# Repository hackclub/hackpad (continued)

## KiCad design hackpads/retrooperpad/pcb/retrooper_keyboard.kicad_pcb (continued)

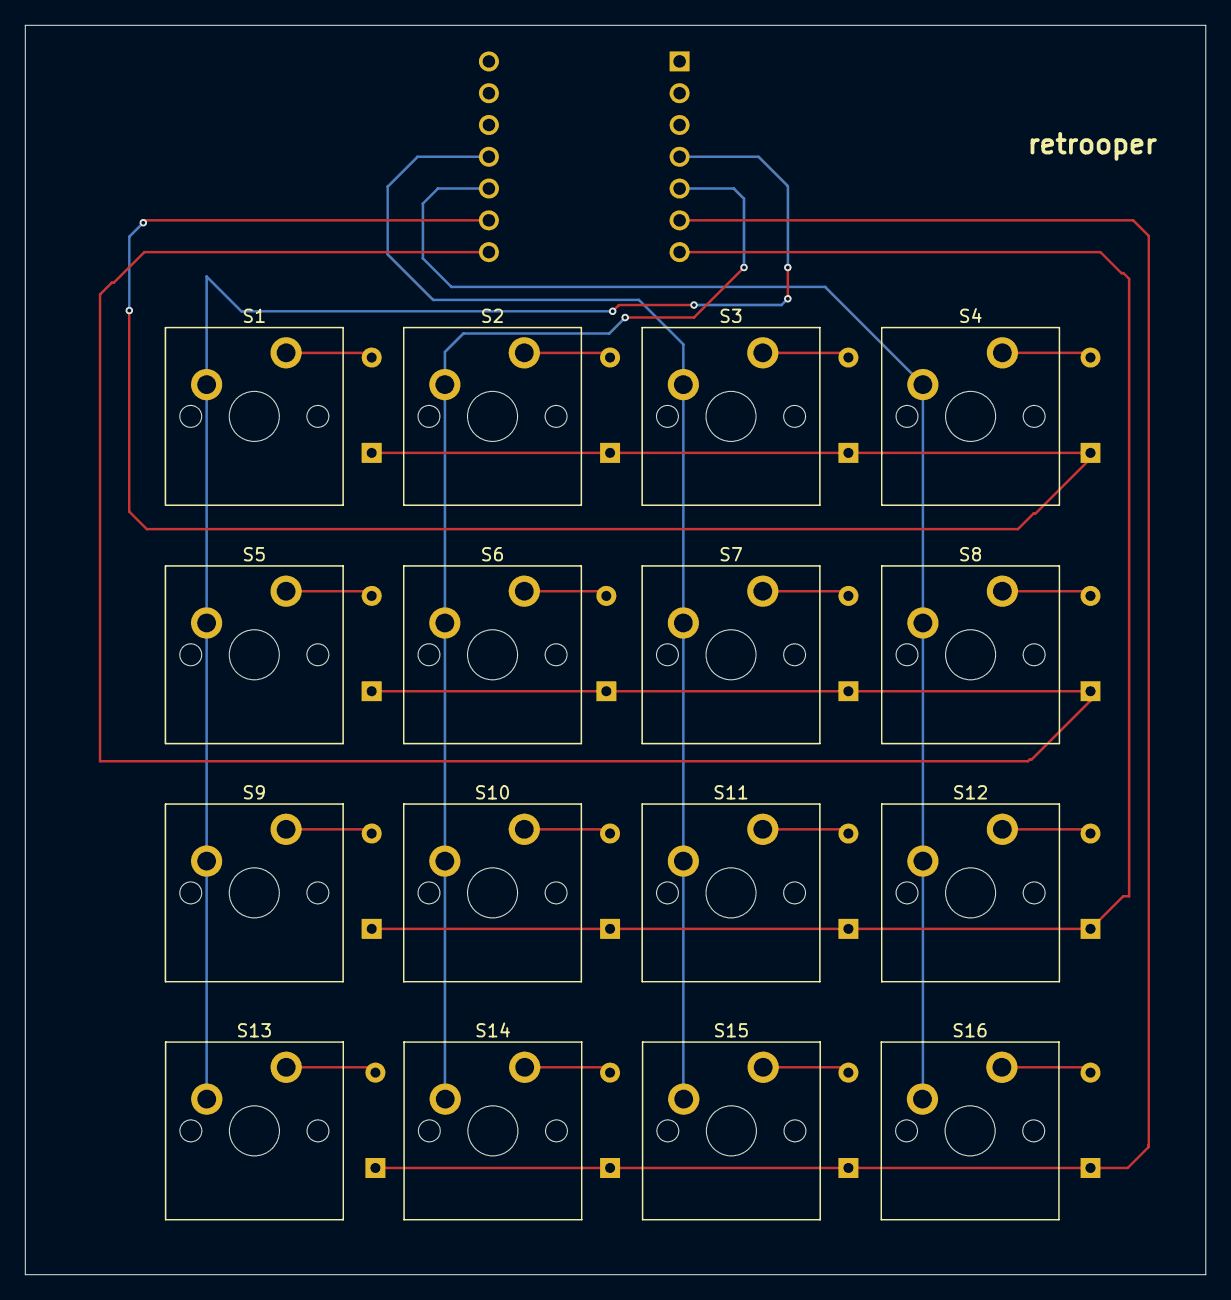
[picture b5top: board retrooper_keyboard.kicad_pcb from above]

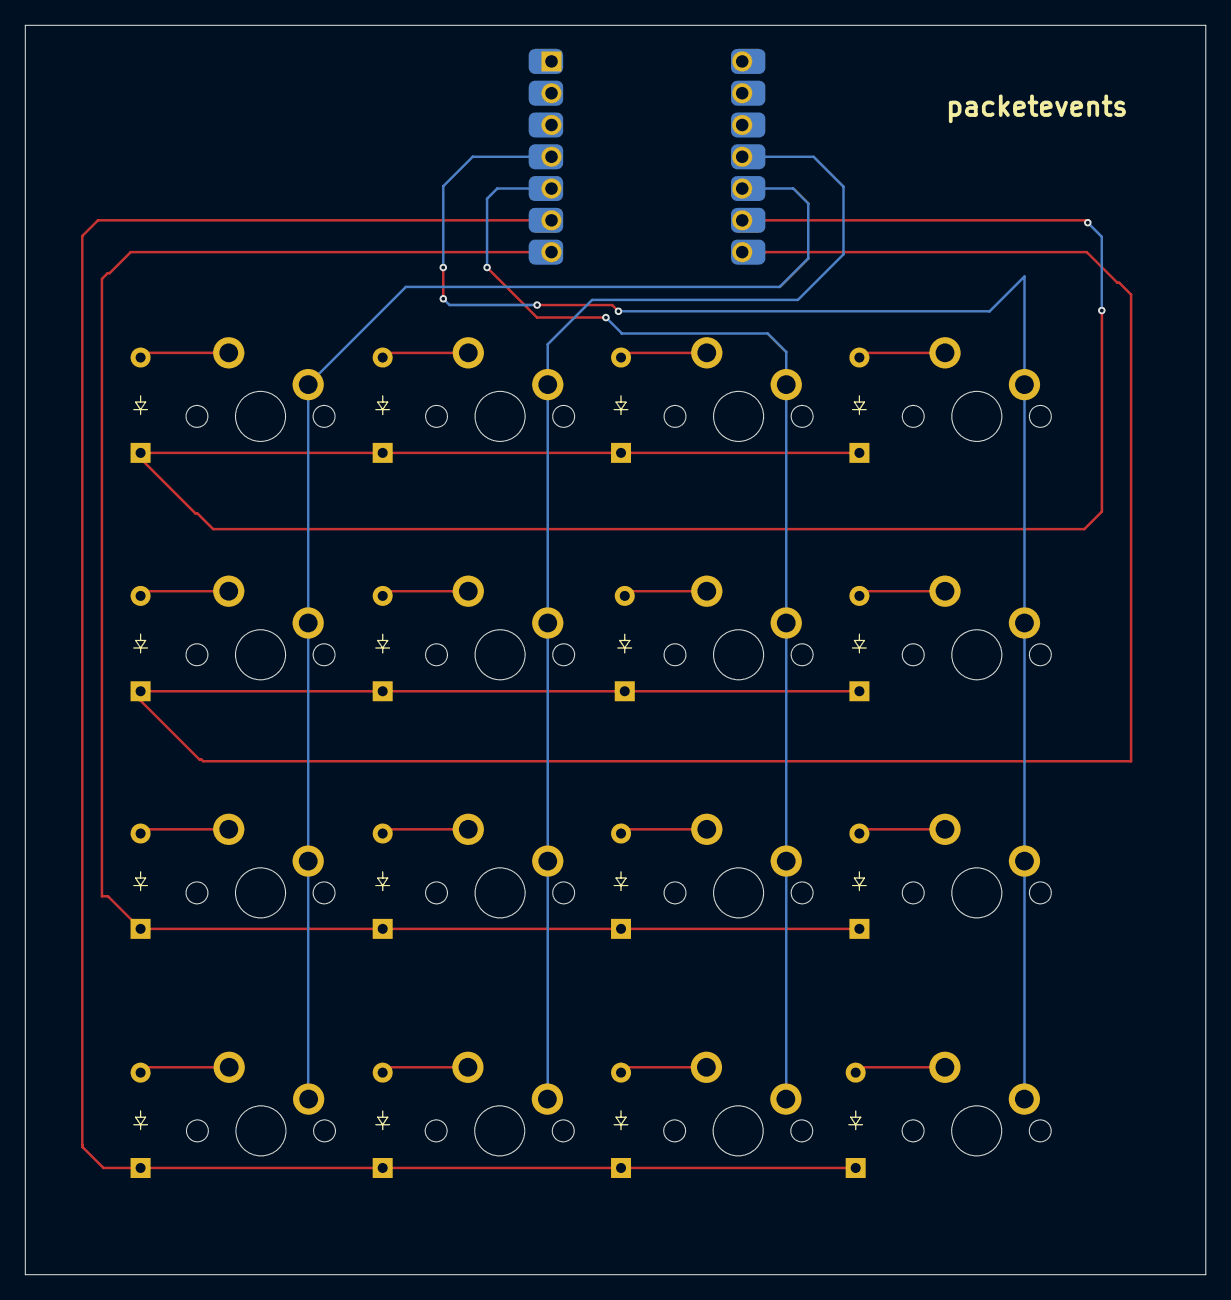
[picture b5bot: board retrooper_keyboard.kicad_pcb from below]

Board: 2 copper layers, 94.3 x 99.8 mm, 33 parts (17 on the bottom side), 24 nets.

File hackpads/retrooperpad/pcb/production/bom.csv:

Designator,Footprint,Quantity,Value,LCSC Part #
"D1, D2, D3, D4, D5, D6, D7, D8, D9",Diode_DO-35,9,Diode,
"S1, S2, S3, S4, S5, S6, S7, S8, S9",MX_PCB_1.00u,9,Keyswitch,
U1,XIAO-SAMD21-RP2040-14P-2.54-21X17.8MM (Seeeduino XIAO),1,Seeed Studio XIAO SAMD21,

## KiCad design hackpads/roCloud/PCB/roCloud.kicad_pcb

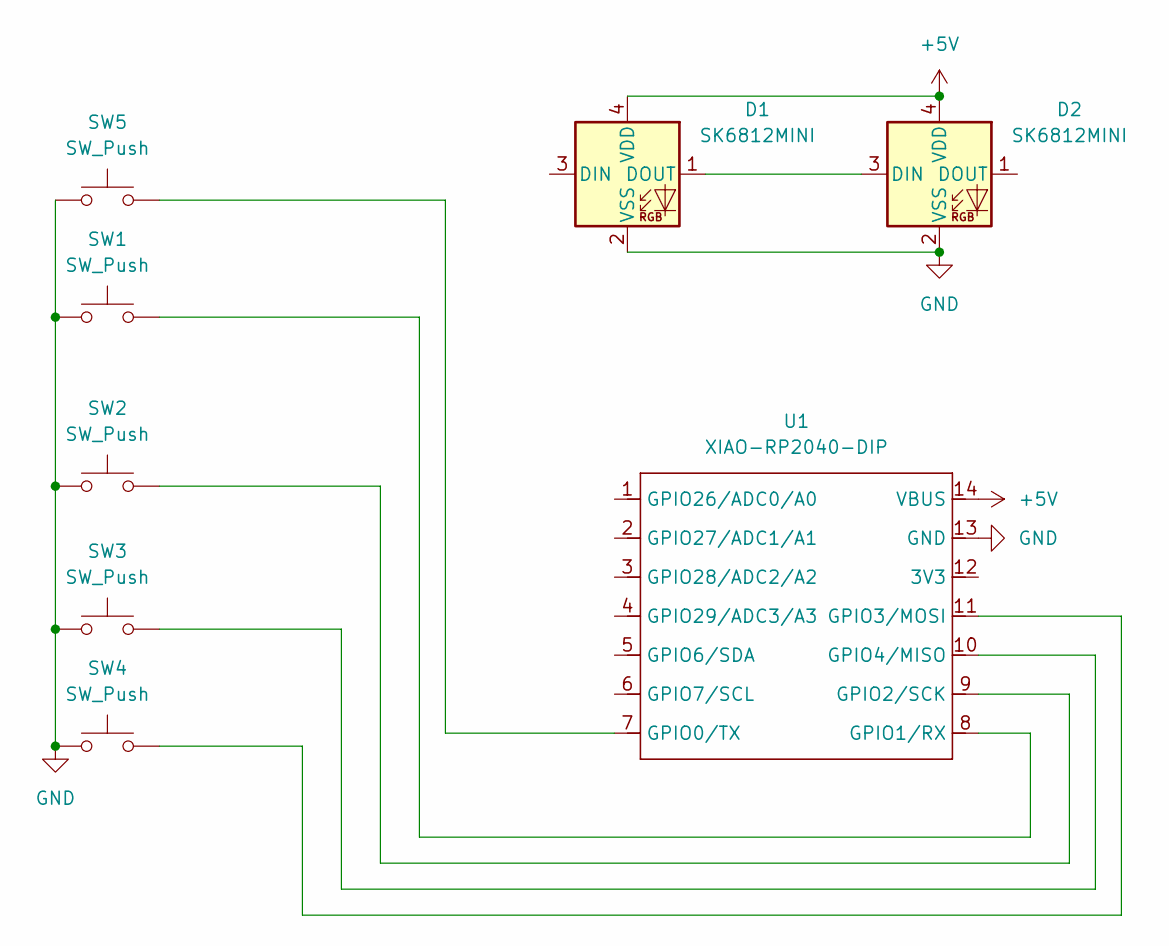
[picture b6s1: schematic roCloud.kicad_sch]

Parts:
D1, D2: SK6812MINI; LED_SK6812MINI_PLCC4_3.5x3.5mm_P1.75mm
SW1, SW2, SW3, SW4, SW5: SW_Push; SW_Cherry_MX_1.00u_PCB
U1: XIAO-RP2040-DIP

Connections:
+5V: D1.4 (VDD), D2.4 (VDD), U1.14 (VBUS)
GND: D1.2 (VSS), D2.2 (VSS), SW1.1, SW2.1, SW3.1, SW4.1, SW5.1, U1.13 (GND)
unnamed: D1.3 (DIN), U1.5 (GPIO6/SDA)
unnamed: D1.1 (DOUT), D2.3 (DIN)
unnamed: SW5.2, U1.7 (GPIO0/TX)
unnamed: SW1.2, U1.8 (GPIO1/RX)
unnamed: SW2.2, U1.9 (GPIO2/SCK)
unnamed: SW4.2, U1.11 (GPIO3/MOSI)
unnamed: SW3.2, U1.10 (GPIO4/MISO)

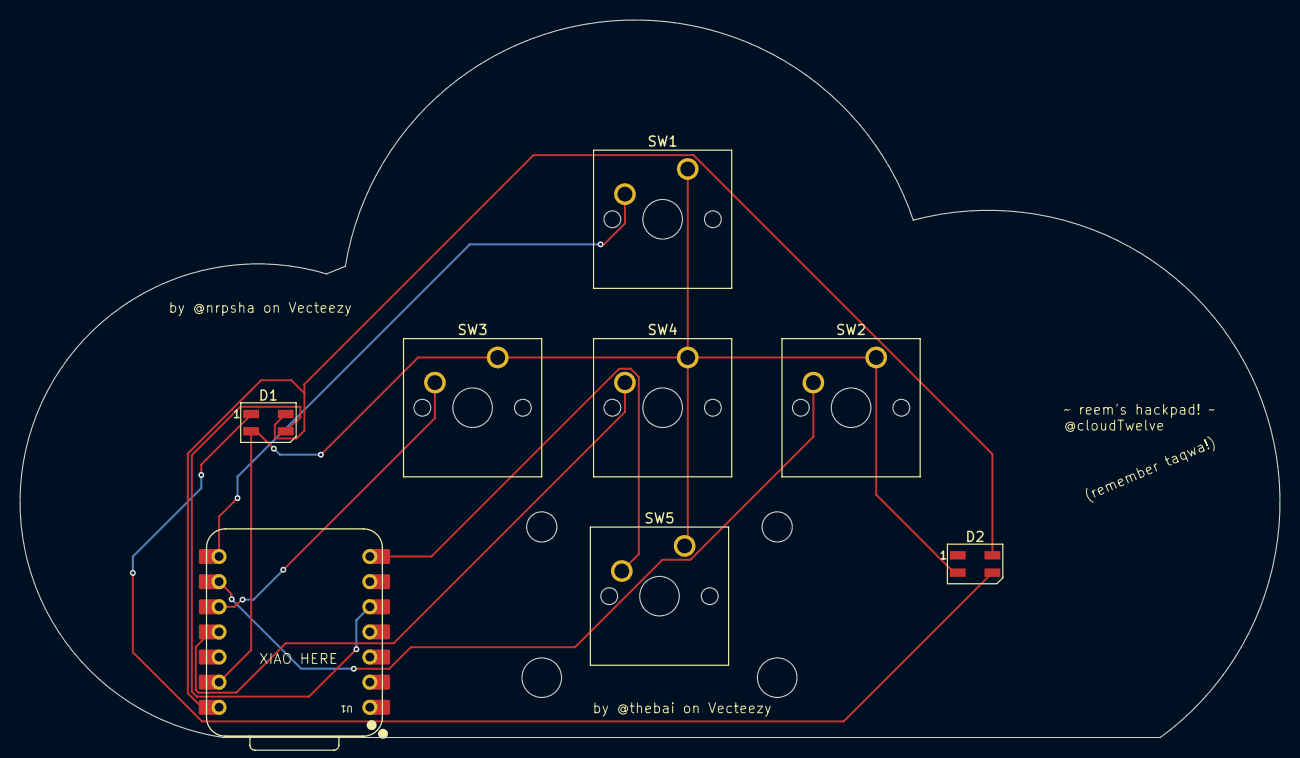
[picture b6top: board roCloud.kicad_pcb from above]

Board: 2 copper layers, 127.4 x 72.5 mm, 10 parts (0 on the bottom side), 9 nets.

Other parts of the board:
!!: LOGO
!!#2: LOGO

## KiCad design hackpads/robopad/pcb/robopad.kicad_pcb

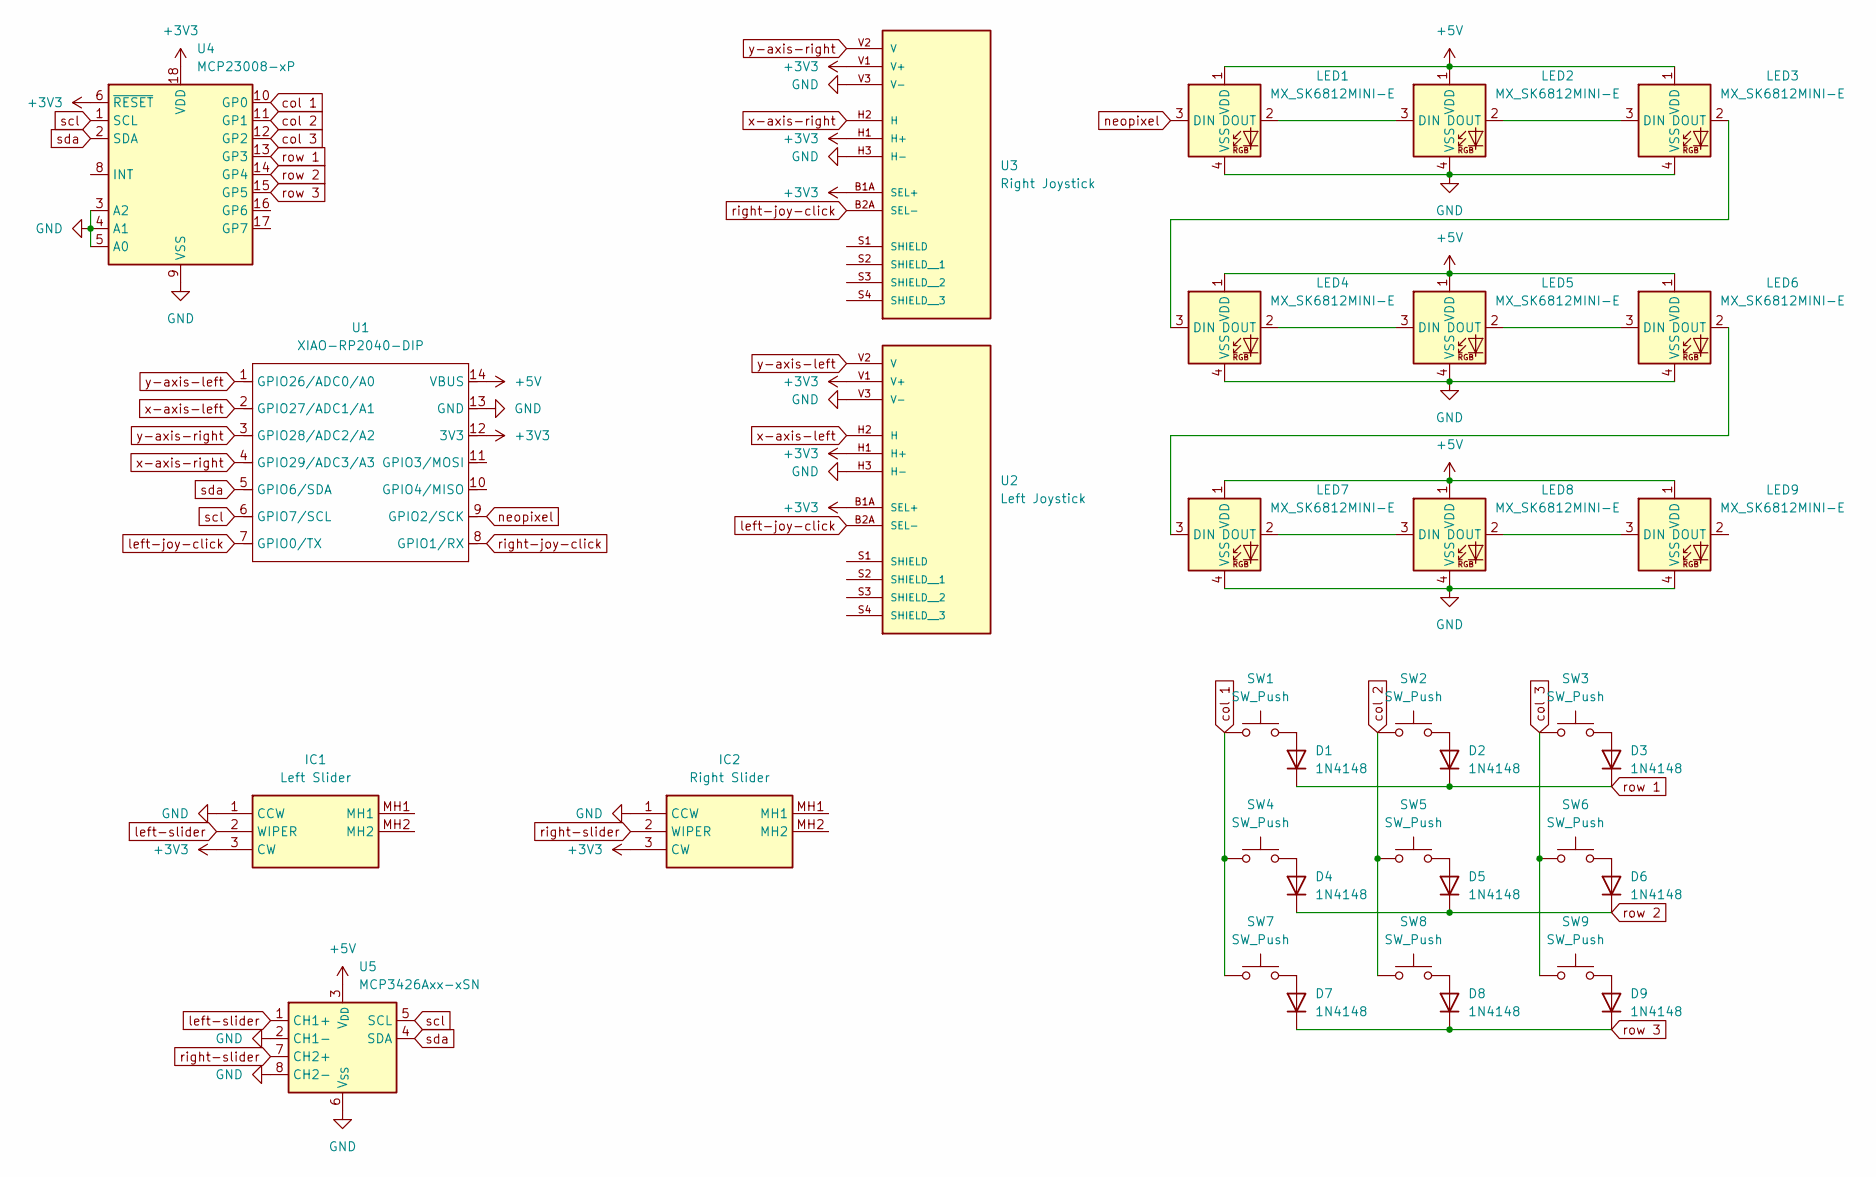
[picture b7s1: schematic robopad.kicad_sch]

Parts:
D1, D2, D3, D4, D5, D6, D7, D8, D9: 1N4148; D_DO-35_SOD27_P7.62mm_Horizontal
IC1: Left Slider; RS30111AC00V; Mouser Part Number 688-RS30111AC00V
IC2: Right Slider; RS30111AC00V; Mouser Part Number 688-RS30111AC00V
LED1, LED2, LED3, LED4, LED5, LED6, LED7, LED8, LED9: MX_SK6812MINI-E; LED_MX_6028R
SW1, SW2, SW3, SW4, SW5, SW6, SW7, SW8, SW9: SW_Push; SW_Cherry_MX_PCB_1.00u
U1: XIAO-RP2040-DIP; XIAO-SAMD21-DIP
U2: Left Joystick; XDCR_COM-09032; PARTREV N/A
U3: Right Joystick; XDCR_COM-09032; PARTREV N/A
U4: MCP23008-xP; DIP-18_W7.62mm
U5: MCP3426Axx-xSN; SOIC-8_3.9x4.9mm_P1.27mm

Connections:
+3V3: IC1.3 (CW), IC2.3 (CW), U1.12 (3V3), U2.B1A (SEL+), U2.H1 (H+), U2.V1 (V+), U3.B1A (SEL+), U3.H1 (H+), U3.V1 (V+), U4.6 (~RESET), U4.18 (VDD)
+5V: LED1.1 (VDD), LED2.1 (VDD), LED3.1 (VDD), LED4.1 (VDD), LED5.1 (VDD), LED6.1 (VDD), LED7.1 (VDD), LED8.1 (VDD), LED9.1 (VDD), U1.14 (VBUS), U5.3 (V_{DD})
GND: IC1.1 (CCW), IC2.1 (CCW), LED1.4 (VSS), LED2.4 (VSS), LED3.4 (VSS), LED4.4 (VSS), LED5.4 (VSS), LED6.4 (VSS), LED7.4 (VSS), LED8.4 (VSS), LED9.4 (VSS), U1.13 (GND), U2.H3 (H-), U2.V3 (V-), U3.H3 (H-), U3.V3 (V-), U4.3 (A2), U4.4 (A1), U4.5 (A0), U4.9 (VSS), U5.2 (CH1-), U5.6 (V_{SS}), U5.8 (CH2-)
unnamed: D1.2 (A), SW1.2
unnamed: D2.2 (A), SW2.2
unnamed: D3.2 (A), SW3.2
unnamed: D4.2 (A), SW4.2
unnamed: D5.2 (A), SW5.2
unnamed: D6.2 (A), SW6.2
unnamed: D7.2 (A), SW7.2
unnamed: D8.2 (A), SW8.2
unnamed: D9.2 (A), SW9.2
unnamed: LED1.2 (DOUT), LED2.3 (DIN)
unnamed: LED2.2 (DOUT), LED3.3 (DIN)
unnamed: LED3.2 (DOUT), LED4.3 (DIN)
unnamed: LED4.2 (DOUT), LED5.3 (DIN)
unnamed: LED5.2 (DOUT), LED6.3 (DIN)
unnamed: LED6.2 (DOUT), LED7.3 (DIN)
unnamed: LED7.2 (DOUT), LED8.3 (DIN)
unnamed: LED8.2 (DOUT), LED9.3 (DIN)
col 1: SW1.1, SW4.1, SW7.1, U4.10 (GP0)
col 2: SW2.1, SW5.1, SW8.1, U4.11 (GP1)
col 3: SW3.1, SW6.1, SW9.1, U4.12 (GP2)
left-joy-click: U1.7 (GPIO0/TX), U2.B2A (SEL-)
left-slider: IC1.2 (WIPER), U5.1 (CH1+)
neopixel: LED1.3 (DIN), U1.9 (GPIO2/SCK)
right-joy-click: U1.8 (GPIO1/RX), U3.B2A (SEL-)
right-slider: IC2.2 (WIPER), U5.7 (CH2+)
row 1: D1.1 (K), D2.1 (K), D3.1 (K), U4.13 (GP3)
row 2: D4.1 (K), D5.1 (K), D6.1 (K), U4.14 (GP4)
row 3: D7.1 (K), D8.1 (K), D9.1 (K), U4.15 (GP5)
scl: U1.6 (GPIO7/SCL), U4.1 (SCL), U5.5 (SCL)
sda: U1.5 (GPIO6/SDA), U4.2 (SDA), U5.4 (SDA)
x-axis-left: U1.2 (GPIO27/ADC1/A1), U2.H2 (H)
x-axis-right: U1.4 (GPIO29/ADC3/A3), U3.H2 (H)
y-axis-left: U1.1 (GPIO26/ADC0/A0), U2.V2 (V)
y-axis-right: U1.3 (GPIO28/ADC2/A2), U3.V2 (V)

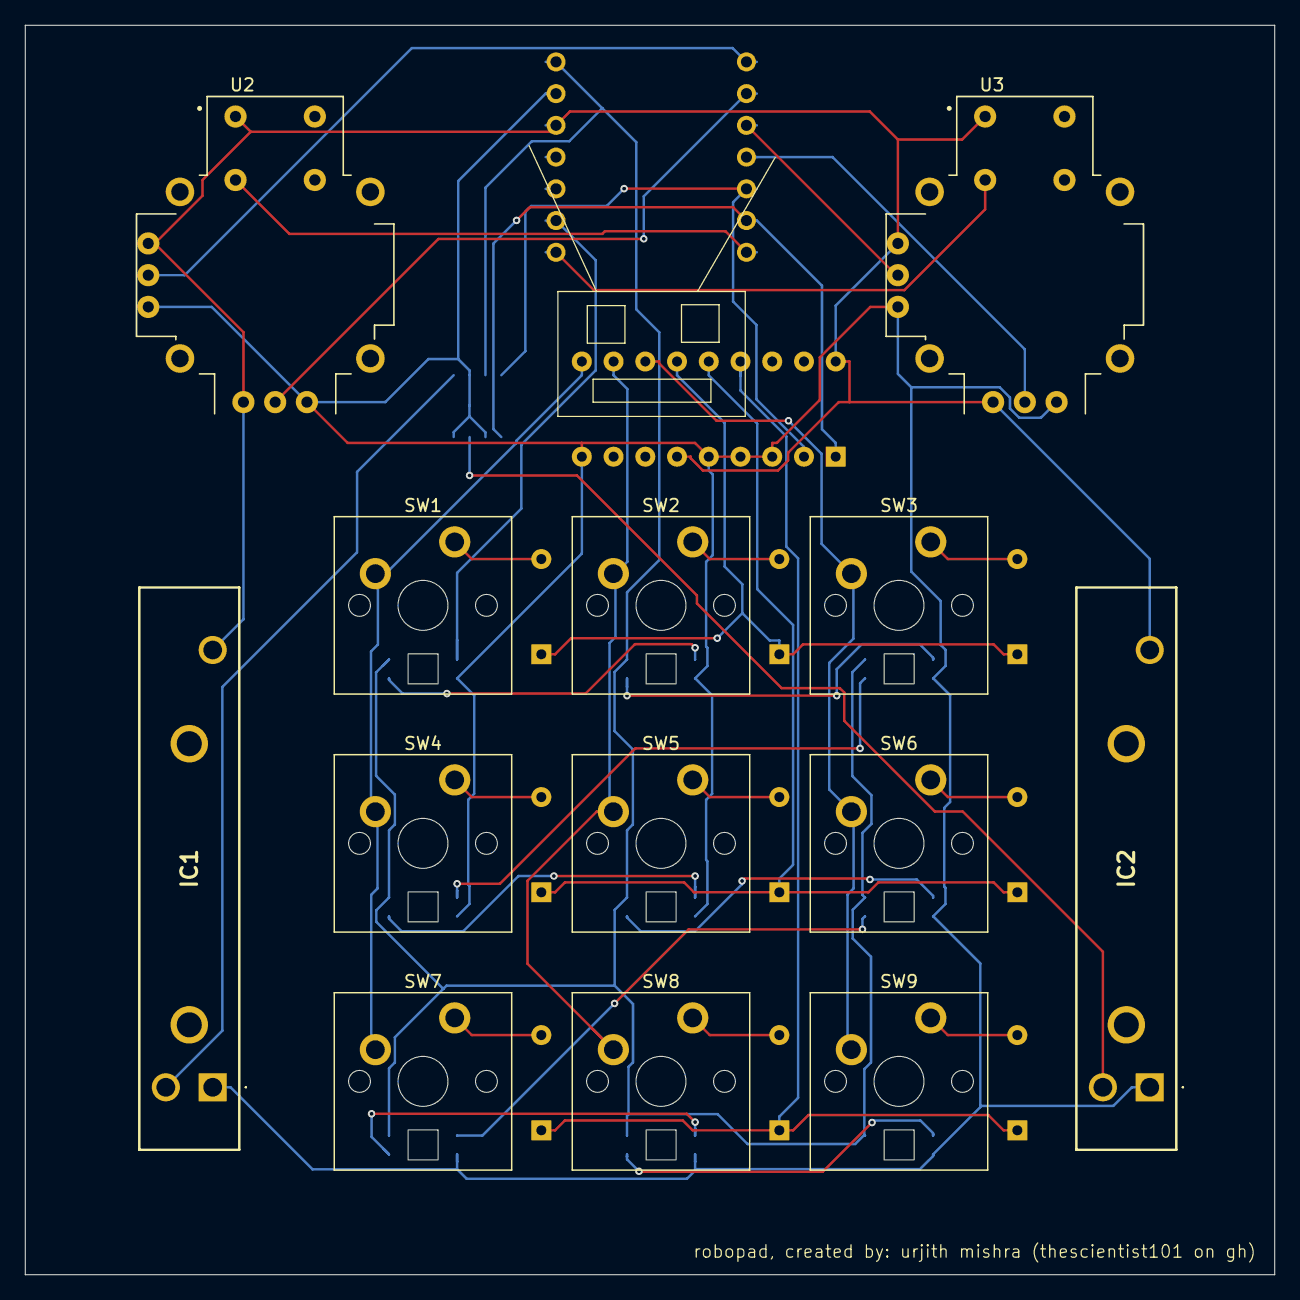
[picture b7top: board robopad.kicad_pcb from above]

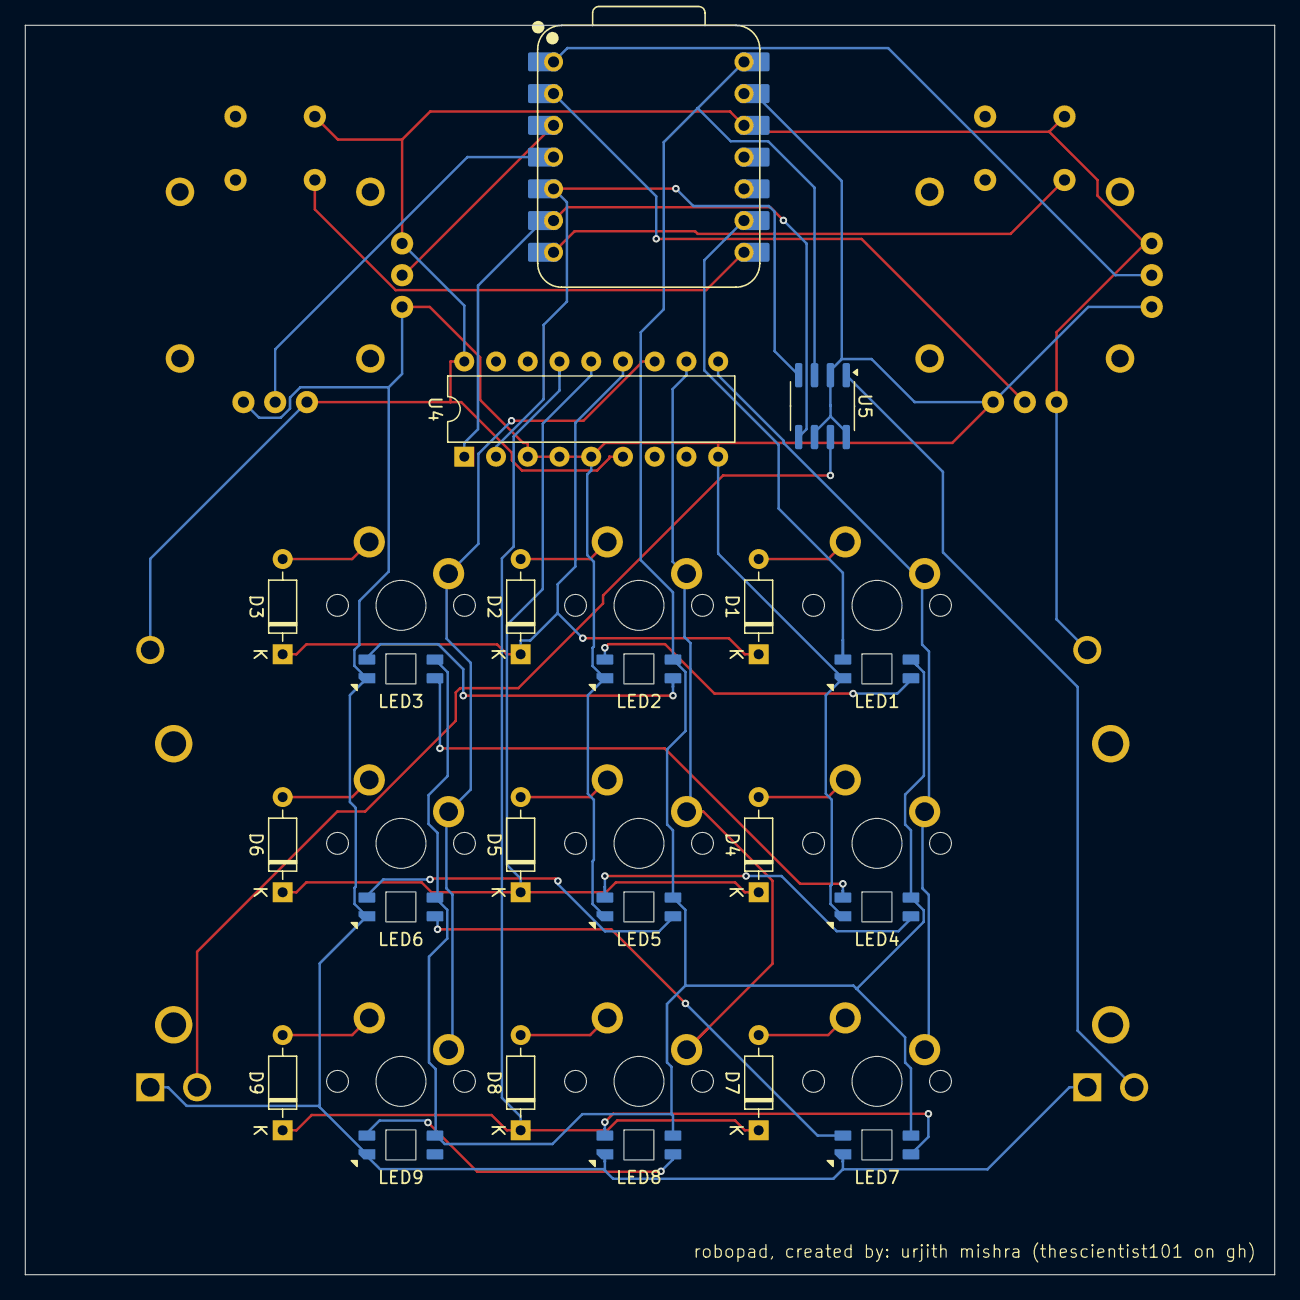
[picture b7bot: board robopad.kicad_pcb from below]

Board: 2 copper layers, 100.0 x 100.0 mm, 34 parts (21 on the bottom side), 37 nets.

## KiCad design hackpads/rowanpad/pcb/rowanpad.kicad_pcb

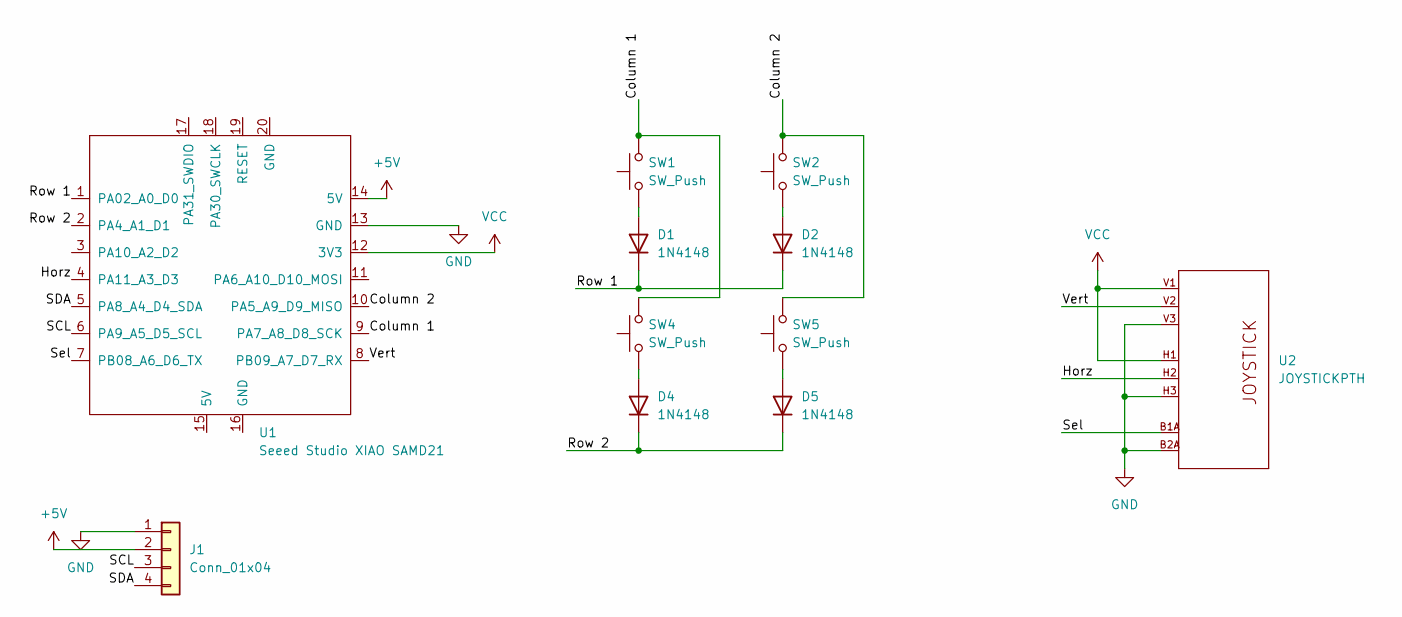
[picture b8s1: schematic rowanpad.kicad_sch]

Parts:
D1, D2, D4, D5: 1N4148; D_DO-35_SOD27_P7.62mm_Horizontal
J1: Conn_01x04; SSD1306-0.91-OLED-4pin-128x32
SW1, SW2, SW4, SW5: SW_Push; SW_Cherry_MX_1.00u_PCB
U1: Seeed Studio XIAO SAMD21; XIAO-Generic-Thruhole-14P-2.54-21X17.8MM
U2: JOYSTICKPTH; JOYSTICK

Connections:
+5V: J1.2, U1.14 (5V)
/Column 1: SW1.2, SW4.2, U1.9 (PA7_A8_D8_SCK)
/Column 2: SW2.2, SW5.2, U1.10 (PA5_A9_D9_MISO)
/Horz: U1.4 (PA11_A3_D3), U2.H2 (H)
/Row 1: D1.1 (K), D2.1 (K), U1.1 (PA02_A0_D0)
/Row 2: D4.1 (K), D5.1 (K), U1.2 (PA4_A1_D1)
/SCL: J1.3, U1.6 (PA9_A5_D5_SCL)
/SDA: J1.4, U1.5 (PA8_A4_D4_SDA)
/Sel: U1.7 (PB08_A6_D6_TX), U2.B1A (SEL+)
/Vert: U1.8 (PB09_A7_D7_RX), U2.V2 (V)
GND: J1.1, U1.13 (GND), U2.B2A (SEL-), U2.H3 (H-), U2.V3 (V-)
unnamed: D1.2 (A), SW1.1
unnamed: D2.2 (A), SW2.1
unnamed: D4.2 (A), SW4.1
unnamed: D5.2 (A), SW5.1
VCC: U1.12 (3V3), U2.H1 (H+), U2.V1 (V+)

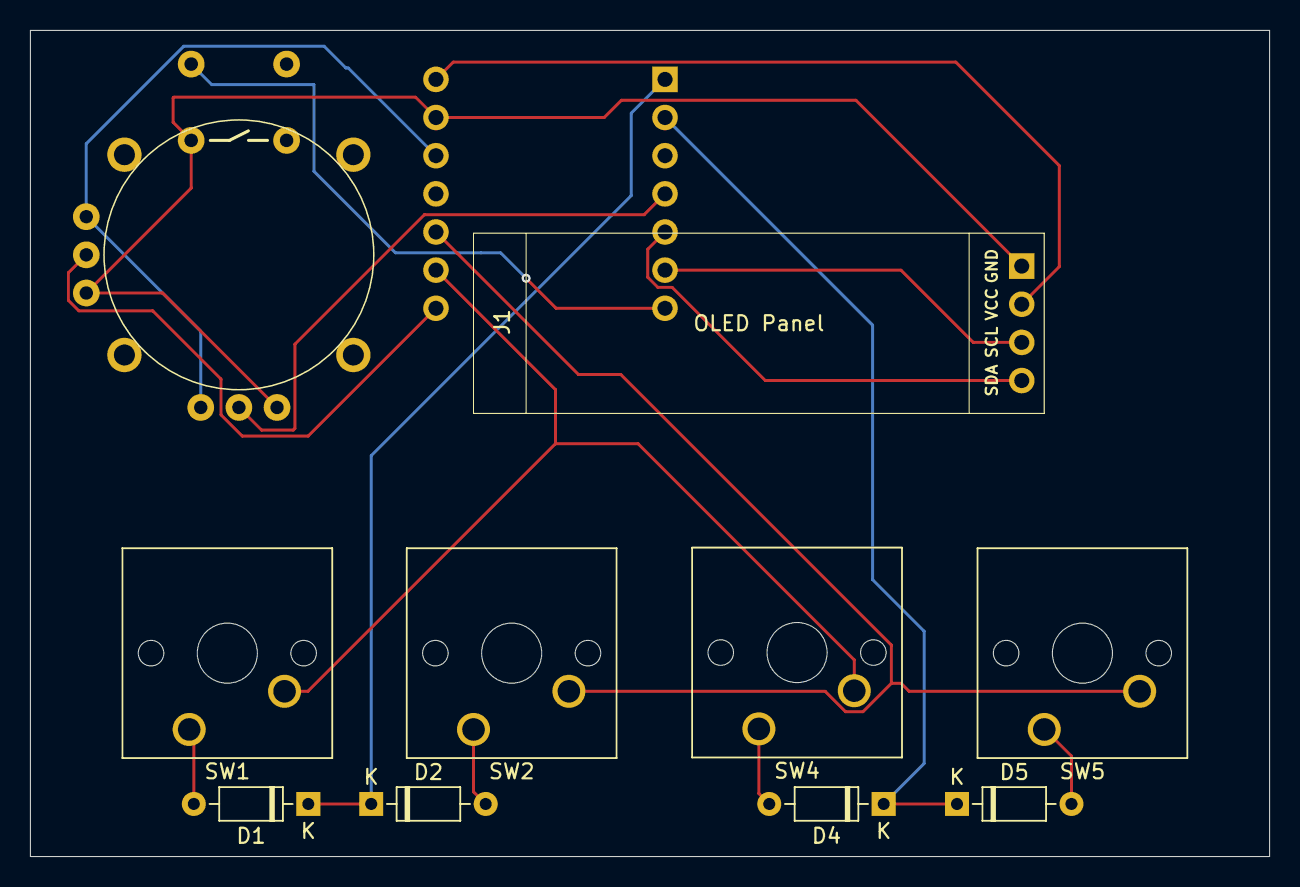
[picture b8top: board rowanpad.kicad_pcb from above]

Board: 2 copper layers, 82.5 x 55.0 mm, 11 parts (1 on the bottom side), 16 nets.
